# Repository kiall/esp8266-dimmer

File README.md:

ESP8266 Light Dimmer
====================

KiCad Schematic and PCB Design for a ESP8266 / ESP-03 based light dimmer.

Tested as working - see revision history for more.

## Board Images

Front:

Back:

## Revision History:

### v1.2:

v1.2 is tested as working.

Fixes:

* Fix PSU Ordering - Secondary DC + and - pins swapped.
* U3 pad size corrected
* C3 470uF footprint corrected
* Add 3v3 + GND power inputs for programming without a mains connection
* PCB Layout reworked

Issues Not Yet Fixed:

* More space behind D1 (Triac) would be better, to allow for a larger heatsink.
* 3v3 + GND power inputs for programming without a mains connection should be labeled on the board.
### v1.1:

Fixes:

* Fix Traic Pin Ordering

Issues Not Yet Fixed:

* None

## References

* [Dimming Circuit](https://www.instructables.com/id/Arduino-controlled-light-dimmer-The-circuit/)
* [BoM Generator](https://github.com/SchrodingersGat/KiBoM)

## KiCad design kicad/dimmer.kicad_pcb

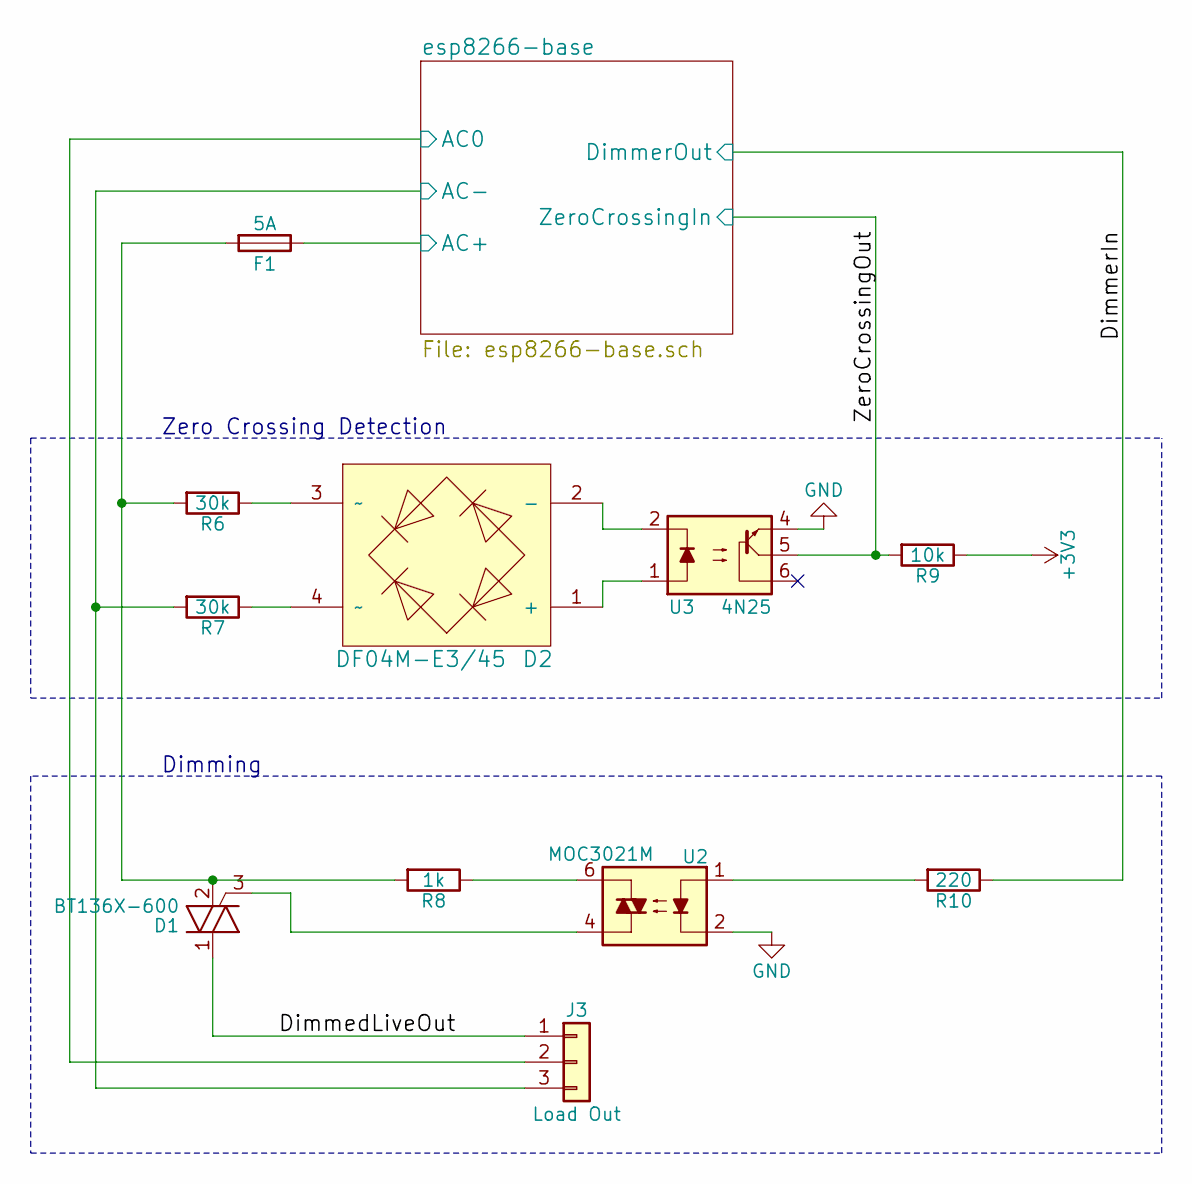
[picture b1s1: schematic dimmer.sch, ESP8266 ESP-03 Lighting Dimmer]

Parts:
D1: BT136X-600; TO-220-3_Vertical
D2: DF04M-E3/45; DF-M
F1: 5A; Fuse_Holder_5x20mm_P15mm
J3: Load Out; RS_Pro_10mm_Pitch_3_Way_PCB_Terminal_Block
R6, R7: 30k; R_Axial_DIN0207_L6.3mm_D2.5mm_P7.62mm_Horizontal
R8: 1k; R_Axial_DIN0207_L6.3mm_D2.5mm_P7.62mm_Horizontal
R9: 10k; R_1206_HandSoldering
R10: 220; R_1206_HandSoldering
U2: MOC3021M; DIP-6_W7.62mm_LongPads
U3: 4N25; SMDIP-6_W9.53mm

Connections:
+3V3: R9.1; also elsewhere on the board
/DimmedLiveOut: D1.1 (A1), J3.1
/DimmerIn: R10.1; also elsewhere on the board
/ZeroCrossingOut: R9.2, U3.5; also elsewhere on the board
/esp8266-base/AC0: J3.2; also elsewhere on the board
/esp8266-base/AC+: F1.1; also elsewhere on the board
/esp8266-base/AC-: J3.3, R7.2; also elsewhere on the board
GND: U2.2, U3.4; also elsewhere on the board
unnamed: D1.2 (A2), F1.2, R6.2, R8.2
unnamed: D1.3 (G), U2.4
unnamed: D2.1 (+), U3.1
unnamed: D2.2 (-), U3.2
unnamed: D2.3 (~~), R6.1
unnamed: D2.4 (~~), R7.1
unnamed: R8.1, U2.6
unnamed: R10.2, U2.1

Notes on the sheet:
Zero Crossing Detection
Dimming

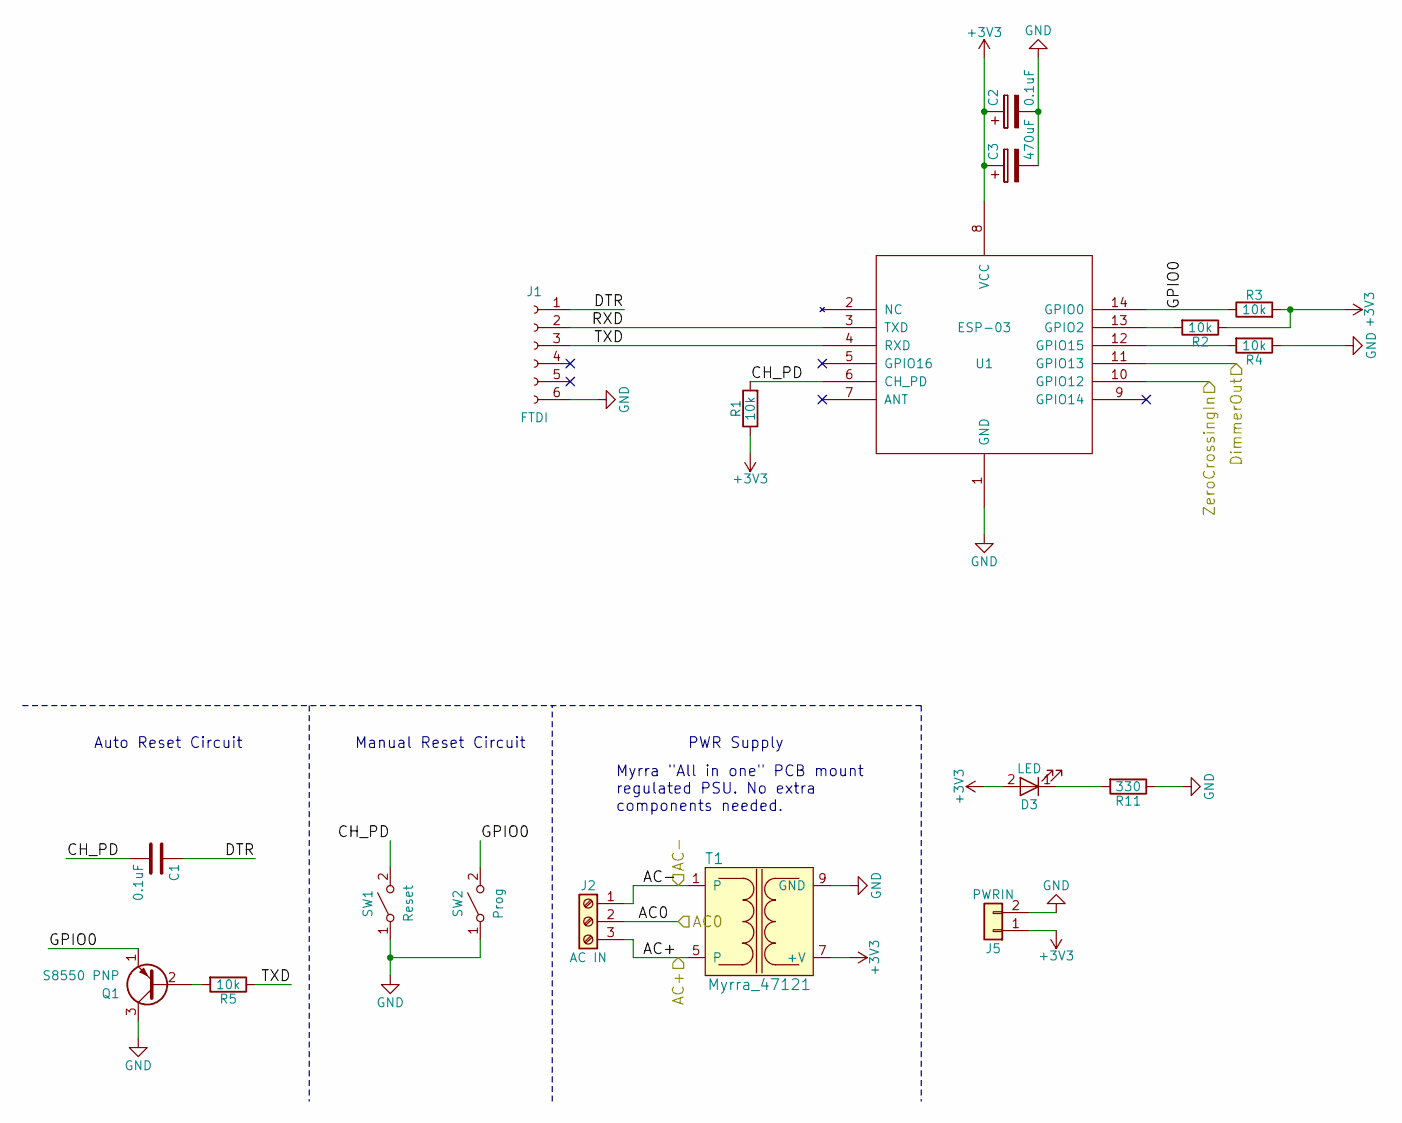
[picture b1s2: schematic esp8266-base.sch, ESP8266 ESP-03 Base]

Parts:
C1, C2: 0.1uF; C_1206_HandSoldering
C3: 470uF; CP_Elec_8x10.5
D3: LED; LED_D4.0mm
J1: FTDI; Socket_Strip_Straight_1x06_Pitch2.54mm
J2: AC IN; RS_Pro_10mm_Pitch_3_Way_PCB_Terminal_Block
J5: PWRIN; Pin_Header_Straight_1x02_Pitch2.54mm
Q1: S8550 PNP; TO-92_Inline_Narrow_Oval
R1, R2, R3, R4, R5: 10k; R_1206_HandSoldering
R11: 330; R_1206_HandSoldering
SW1: Reset; SW_PUSH_6mm
SW2: Prog; SW_PUSH_6mm
T1: Myrra_47121; Transformer_Myrra_47000_1P_1S
U1: ESP-03

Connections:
+3V3: C2.1, C3.1, D3.2 (A), J5.1, R1.1, R2.1, R3.2, T1.7 (+V), U1.8 (VCC); also elsewhere on the board
/DimmerIn: U1.11 (GPIO13); also elsewhere on the board
/ZeroCrossingOut: U1.10 (GPIO12); also elsewhere on the board
/esp8266-base/AC0: J2.2; also elsewhere on the board
/esp8266-base/AC+: J2.3, T1.5; also elsewhere on the board
/esp8266-base/AC-: J2.1, T1.1; also elsewhere on the board
/esp8266-base/CH_PD: C1.2, R1.2, SW1.2 (B), U1.6 (CH_PD)
/esp8266-base/DTR: C1.1, J1.1
/esp8266-base/GPIO0: Q1.1 (E), R3.1, SW2.2 (B), U1.14 (GPIO0)
/esp8266-base/RXD: J1.2, U1.3 (TXD)
/esp8266-base/TXD: J1.3, R5.1, U1.4 (RXD)
GND: C2.2, C3.2, J1.6, J5.2, Q1.3 (C), R4.1, R11.1, SW1.1 (A), SW2.1 (A), T1.9 (GND), U1.1 (GND); also elsewhere on the board
unnamed: D3.1 (K), R11.2
unnamed: Q1.2 (B), R5.2
unnamed: R2.2, U1.13 (GPIO2)
unnamed: R4.2, U1.12 (GPIO15)

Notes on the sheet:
Auto Reset Circuit
Manual Reset Circuit
PWR Supply
Myrra "All in one" PCB mount regulated PSU. No extra components needed.

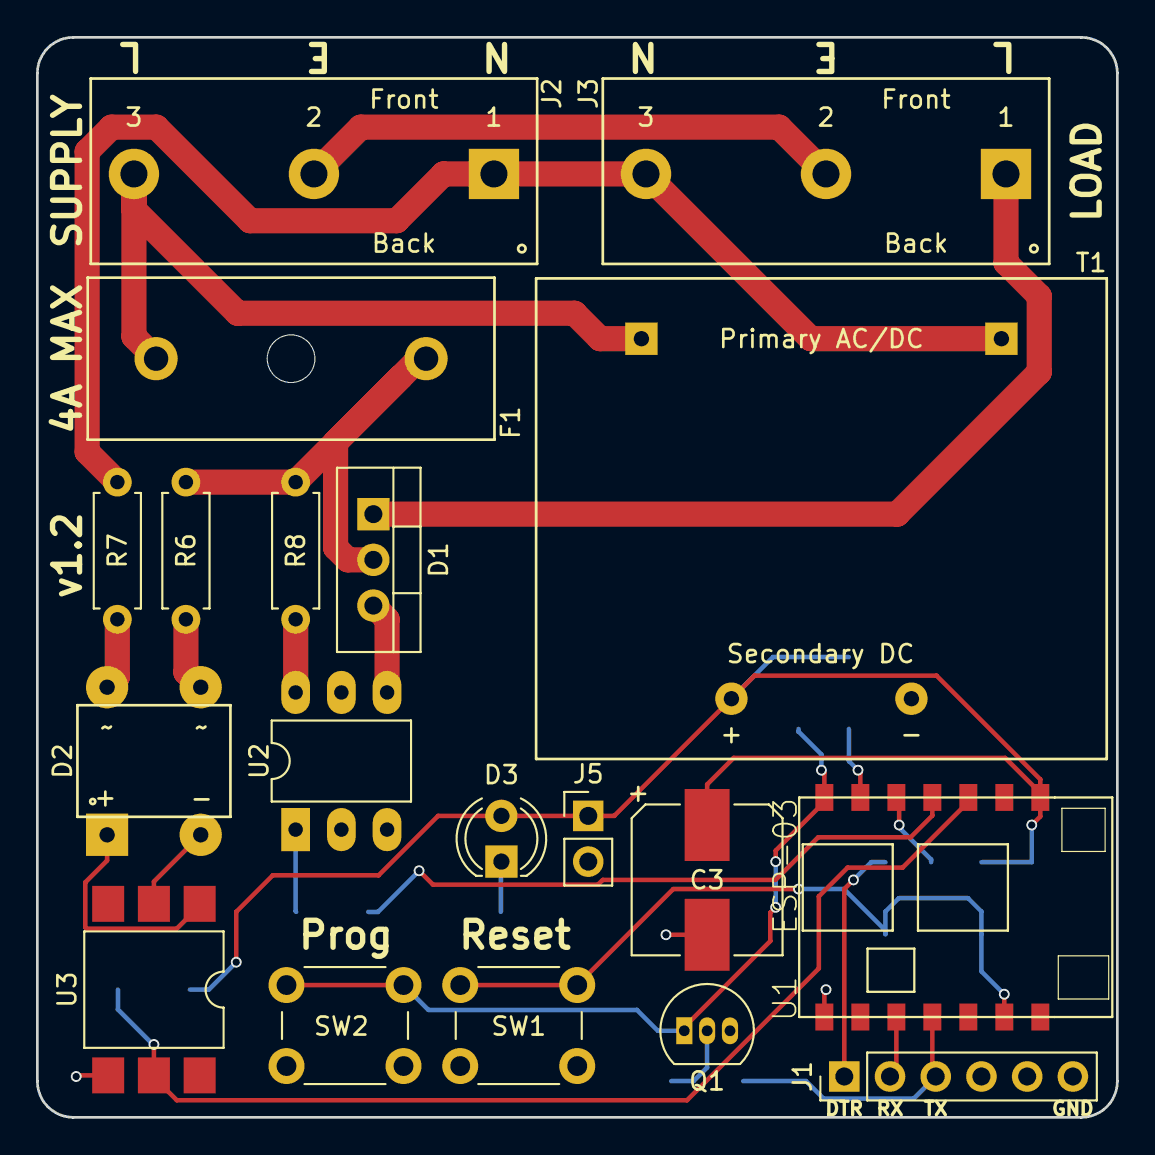
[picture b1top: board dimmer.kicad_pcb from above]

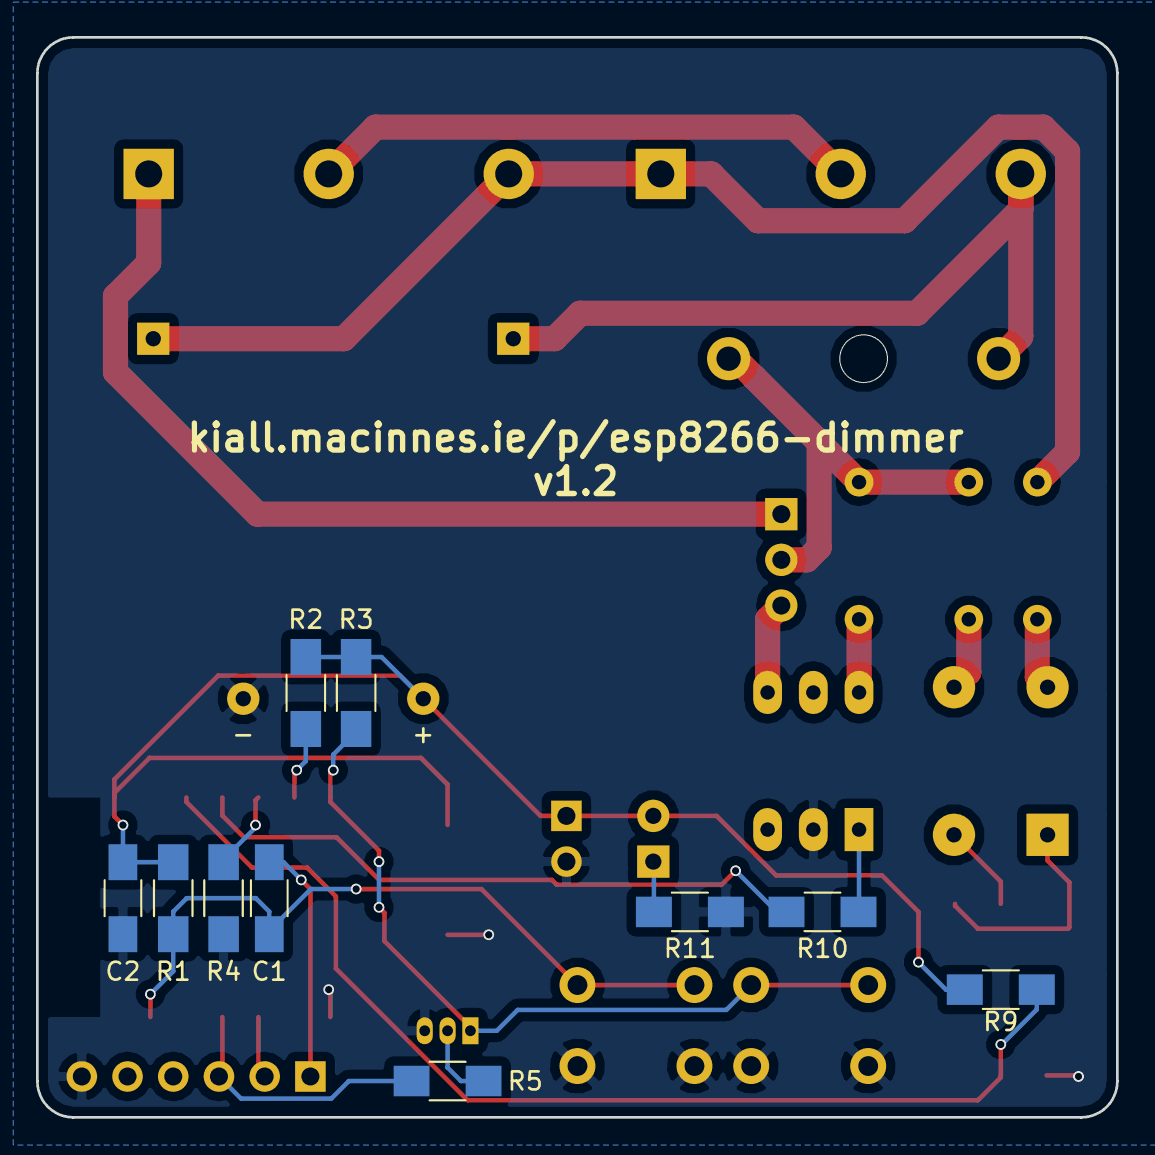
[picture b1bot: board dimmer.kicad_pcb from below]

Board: 2 copper layers, 60.0 x 60.0 mm, 29 parts (10 on the bottom side), 25 nets.

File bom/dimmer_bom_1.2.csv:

Component,Description,Part,References,Value,Footprint,Quantity Per PCB,Datasheet
1,Unpolarized capacitor,C,C1,0.1uF,C_1206_HandSoldering,1,
2,Polarised capacitor,CP,C2,0.1uF,C_1206_HandSoldering,1,
3,Polarised capacitor,CP,C3,470uF,CP_Elec_8x10.5,1,
4,triode for alternating current (TRIAC),Q_TRIAC_AAG,D1,BT136X-600,TO-220-3_Vertical,1,
5,"Diode bridge (pins: 1=+, 2=-, 3=AC, 4=AC)",DF04M-E3/45,D2,DF04M-E3/45,DF-M,1,
6,LED generic,LED,D3,LED,LED_D4.0mm,1,
7,"Fuse, generic",Fuse,F1,5A,Fuse_Holder_5x20mm_P15mm,1,
8,"Generic screw terminal, single row, 01x03",Screw_Terminal_01x03,J2,AC IN,RS_Pro_10mm_Pitch_3_Way_PCB_Terminal_Block,1,
9,"Generic connector, single row, 01x06",Conn_01x06_Female,J1,FTDI,Socket_Strip_Straight_1x06_Pitch2.54mm,1,
10,"Generic connector, single row, 01x03",Conn_01x03,J3,Load Out,RS_Pro_10mm_Pitch_3_Way_PCB_Terminal_Block,1,
11,"Generic connector, single row, 01x02",Conn_01x02,J5,PWRIN,Pin_Header_Straight_1x02_Pitch2.54mm,1,
12,Transistor PNP (general),Q_PNP_EBC,Q1,S8550 PNP,TO-92_Inline_Narrow_Oval,1,
13,Resistor,R,R1 R2 R3 R4 R5 R9,10k,R_1206_HandSoldering,6,
14,Resistor,R,R8,1k,R_Axial_DIN0207_L6.3mm_D2.5mm_P7.62mm_Horizontal,1,
15,Resistor,R,R10,220,R_1206_HandSoldering,1,
16,Resistor,R,R6 R7,30k,R_Axial_DIN0207_L6.3mm_D2.5mm_P7.62mm_Horizontal,2,
17,Resistor,R,R11,330,R_1206_HandSoldering,1,
18,Single Pole Single Throw (SPST) switch,SW_SPST,SW2,Prog,SW_PUSH_6mm,1,
19,Single Pole Single Throw (SPST) switch,SW_SPST,SW1,Reset,SW_PUSH_6mm,1,
20,"Transformer, single primary, single output, regulated",Transformer_Myrra_47000_1P_1S,T1,Myrra_47121,Transformer_Myrra_47000_1P_1S,1,
21,"DC Optocoupler Base Connected, Vce 30V, CTR 20%, Viso 2500V, DIP6",4N25,U3,4N25,SMDIP-6_W9.53mm,1,https://www.vishay.com/docs/83725/4n25.pdf
22,"ESP8266 ESP-03 module, 14 pins, 2mm, ceramic antenna",ESP-03,U1,ESP-03,ESP-03,1,http://l0l.org.uk/2014/12/esp8266-modules-hardware-guide-got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
23,"Random Phase Opto-Triac, Vdrm 250V, Ift 15mA, DIP6",MOC3021M,U2,MOC3021M,DIP-6_W7.62mm_LongPads,1,http://www.fairchildsemi.com/ds/MO/MOC3020M.pdf





Component Groups:,23
Component Count:,29
Fitted Components:,29
Number of PCBs:,1
Total components:,29
Schematic Version:,1.2
Schematic Date:,
BoM Date:,Sat 14 Oct 2017 14:27:09 IST
Schematic Source:,/home/kiall/kicad/projects/esp8266-dimmer/kicad/dimmer.sch
KiCad Version:,Eeschema 4.0.7

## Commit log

2017-09-17 Add Gerber files
2017-09-17 Add Bill of Materials
2017-09-17 Fix links
2017-09-17 Add some images
2017-09-17 Add BoM in text format
2017-09-17 Add some more descriptive text
2017-09-17 Add HK
    Someone I know has a "problem" with HK ;)
2017-09-17 Rev 1.1: Fix triac connections
    Pins 1 and 2 on the triac D1 were connected in backwords, preventing
    the circuit from working.
2017-10-14 Update for v1.2 - Fixes and board redesign
2017-10-15 Update 1.2 gerbers
2017-11-17 Mark v1.2 as tested+working
2017-11-17 Add Firmware source
2017-11-17 add note on v1.2 labeling
